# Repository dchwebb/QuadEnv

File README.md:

# QuadEnv/L4O

Overview
--------

QuadEnv is a four-voice polyphonic ADSR envelope generator designed for use with the Eurorack Modular Synthesiser architecture. L4O is a four-voice sine wave LFO and uses the same hardware as QuadEnv.

Different front panels are provided for each mode, while the firmware, component and controls boards are dual mode.

As part of a range of compatilble Mountjoy Modular modules, polyphonic interconnections are made using RJ-45 cables (as used for Ethernet).

A USB serial console is provided for customising the envelope times and fade-in rates of the LFOs.

The third potentiometer (Sustain or Fade-In) has a momentary button which allows switching between the envelope and LFO modes via a long press.

QuadEnv
-------

The digital envelopes are modelled on a Roland System 100 system, with logarithmic/exponential attack/decay and release sections. The level of each envelope is displayed in a bank of LEDs at the top of the module.

A short press on the Sustain potentiometer button inverts the envelopes.

The USB serial console allows the envelope times to be scaled up or down for longer or shorter envelopes.

L4O
---

The four potentiometers control Speed, Spread, Fade-in and Level. Spread adjusts the variation in LFO speed from one voice to another. Fade-in allows the LFO level to be increased gradually. Short pressing the Fade-in button allows the speed to also be gradually increased. Fade-in starts when a gate is received at the input.

The USB serial interface allows the fade-in times of the level and speed to be independently adjusted.

Technical
---------

The module is based around an STM32G431 microcontroller which contains four internal 12 bit DACs used to generate the envelopes at approximately 47kHz.

A CD40109B level shifter provides input protection for the Gate In signals. A TL074 op-amp ampilifies the DAC outputs to around 8 volts at maximum.

Construction is a sandwich of three PCBs with a component board, a controls board and a panel. PCBs designed in Kicad v6.

From version 3 LEDs are controlled by PWM to fix no display when under the LED forward voltage.

[Components schematic v3](https://raw.githubusercontent.com/dchwebb/QuadEnv/master/Component_Schematic_v3.pdf)

[Controls schematic v2](https://raw.githubusercontent.com/dchwebb/QuadEnv/master/Control_Schematic.pdf)

### Power

The Eurorack +/-12V rails have reverse polarity protection and filtering. 3.3V rails are generated with a linear regulator.

- +12V Maximum Current Draw: 80mA

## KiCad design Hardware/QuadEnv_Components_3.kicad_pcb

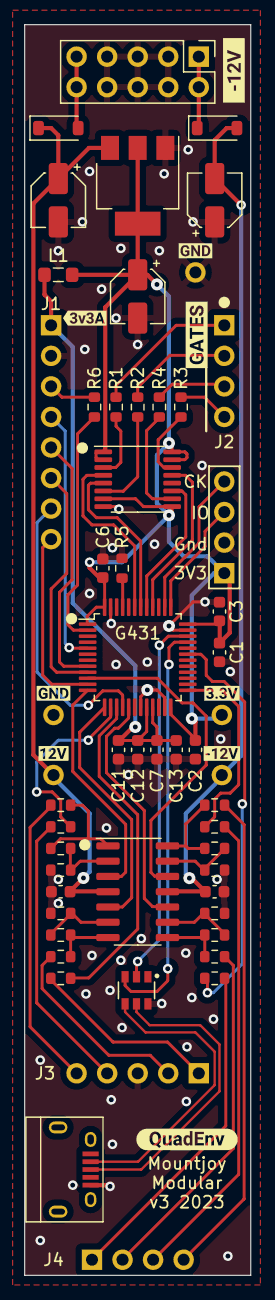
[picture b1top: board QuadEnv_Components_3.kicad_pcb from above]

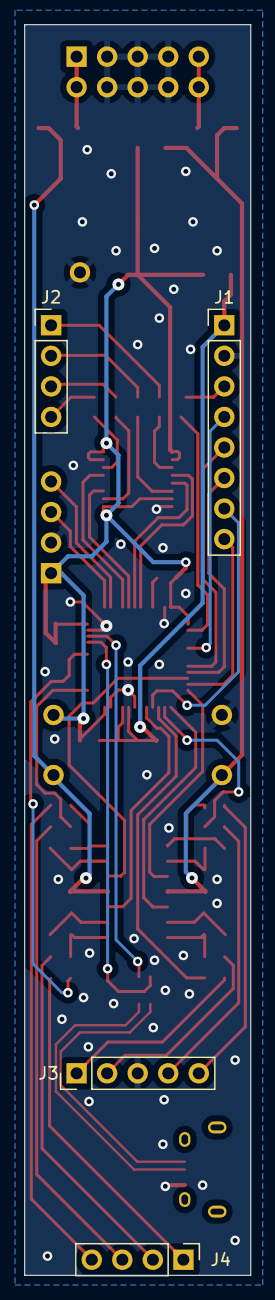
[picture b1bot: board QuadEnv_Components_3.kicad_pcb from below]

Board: 2 copper layers, 18.8 x 104.0 mm, 64 parts (4 on the bottom side), 57 nets.

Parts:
C1: 4.7uF; C_0603_1608Metric
C2, C3, C6, C12: 100nF; C_0603_1608Metric
C4, C5, C8: 22uF; CP_Elec_4x5.8
C7: 10nF; C_0603_1608Metric
C9, C10, C11, C13: 1uF; C_0603_1608Metric
D1, D2: 1N5819; D_SOD-123
J1: Conn_01x08_Male; PinHeader_1x08_P2.54mm_Vertical
J2, J4: Conn_01x04_Male; PinHeader_1x04_P2.54mm_Vertical
J3: Conn_01x05_Male; PinHeader_1x05_P2.54mm_Vertical
J5: SWD_Header; SWD_header
J6: Eurorack_10_pin_power; PinHeader_2x05_P2.54mm_Vertical
J7: USB_B_Micro; USB_Micro-B_Amphenol
L1: L_Small; L_0805_2012Metric_Pad1.05x1.20mm_HandSolder
R1, R2, R3, R4: 10k; R_0603_1608Metric
R5: 100k; R_0603_1608Metric
R6: 510; R_0603_1608Metric
R9, R10, R11, R12: 3k3; R_0603_1608Metric
R13, R14, R15, R16: 4k7; R_0603_1608Metric
R17, R18, R19, R20, R21, R22, R23, R24: 1k; R_0603_1608Metric
TP1, TP2, TP3, TP4, TP5: TestPoint; 1mm_Test_Point
U1: STM32G431C6T6; LQFP-48_7x7mm_P0.5mm
U2: LD1117-3.3-4Tab; SOT-223-3_TabPin2
U3: CD40109B; TSSOP-16_4.4x5mm_P0.65mm
U4: TL074; SOIC-14_3.9x8.7mm_P1.27mm
U5: STF202-22T1G
kibuzzard-64DF8AE0: G***; kibuzzard-64DF8AE0
kibuzzard-640A0C12: G***; kibuzzard-640A0C12
kibuzzard-6409F893: G***; kibuzzard-6409F893
kibuzzard-6409FE2B: G***; kibuzzard-6409FE2B
kibuzzard-6409FE16: G***; kibuzzard-6409FE16
kibuzzard-6409FE46: G***; kibuzzard-6409FE46
kibuzzard-6409FE57, kibuzzard-6409FE57#2: G***; kibuzzard-6409FE57
kibuzzard-6409FEF9: G***; kibuzzard-6409FEF9

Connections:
+3.3V: C1.1, C2.1, C3.1, C6.1, C8.1, J5.1, L1.1, TP2.1, U1.1 (VBAT), U1.24 (VDD), U1.36 (VDD), U1.48 (VDD), U2.2 (VO), U3.1 (Vcc), U3.2 (EN_A), U3.7 (EN_B), U3.9 (EN_C), U3.15 (EN_D), U3.16 (Vdd)
+3.3VA: C7.1, C11.2, C12.2, C13.2, J1.1, L1.2, U1.20 (VREF+), U1.21 (VDDA)
+12V: C4.1, C9.2, D1.1 (K), TP3.1, U2.3 (VI), U4.4 (V+)
-12V: C5.2, C10.2, D2.2 (A), TP4.1, U4.11 (V-)
/+12V_IN: D1.2 (A), J6.9, J6.10
/-12V_IN: D2.1 (K), J6.1, J6.2
/Attack_Pot: J1.5, U1.8 (PA0)
/BOOT0: R5.2, U1.45 (PB8-BOOT0)
/D+: J7.3 (D+), U5.5 (D1_IN)
/D-: J7.2 (D-), U5.4 (D2_IN)
/Decay_Pot: J1.6, U1.9 (PA1)
/Env1_DAC: U1.12 (PA4), U4.3 (+)
/Env1_Out: J3.5, R18.2
/Env2_DAC: U1.13 (PA5), U4.5 (+)
/Env2_Out: J3.2, R20.2
/Env3_DAC: U1.17 (PB1), U4.10 (+)
/Env3_Out: J4.2, R22.2
/Env4_DAC: U1.10 (PA2), U4.12 (+)
/Env4_Out: J4.4, R24.2
/Gate1: U1.43 (PB6), U3.4 (E)
/Gate1_In: J2.1, R1.1
/Gate2: U1.42 (PB5), U3.5 (F)
/Gate2_In: J2.2, R2.1
/Gate3: U1.41 (PB4), U3.11 (G)
/Gate3_In: J2.3, R4.2
/Gate4: U1.40 (PB3), U3.13 (H)
/Gate4_In: J2.4, R3.2
/LED1: R17.1, U1.14 (PA6)
/LED2: R19.1, U1.15 (PA7)
/LED3: R21.1, U1.31 (PA9)
/LED4: R23.1, U1.25 (PB11)
/Led1_Out: J3.4, R17.2
/Led2_Out: J3.1, R19.2
/Led3_Out: J4.1, R21.2
/Led4_Out: J4.3, R23.2
/Mode_Btn: J1.4, U1.5 (PF0-OSC_IN)
/Mode_Led: J1.3, R6.1
/Release_Pot: J1.8, U1.11 (PA3)
/SWCLK: J5.4, U1.38 (PA14)
/SWIO: J5.3, U1.37 (PA13)
/Sustain_Pot: J1.7, U1.16 (PB0)
/USB_DM: U1.33 (PA11), U5.3 (D2_OUT)
/USB_DP: U1.34 (PA12), U5.2 (D1_OUT)
GND: C1.2, C2.2, C3.2, C4.2, C5.1, C6.2, C7.2, C8.2, C9.1, C10.1, C11.1, C12.1, C13.1, J1.2, J3.3, J5.2, J6.3, J6.4, J6.5, J6.6, J6.7, J6.8, J7.5 (GND), R5.1, R9.2, R10.2, R11.2, R12.2, TP1.1, TP5.1, U1.19 (VSSA), U1.23 (VSS), U1.35 (VSS), U1.47 (VSS), U2.1 (GND), U3.8 (Vss), U5.6 (GND)
unnamed: R13.1, R18.1, U4.1
unnamed: R14.1, R20.1, U4.7
unnamed: R15.1, R22.1, U4.8
unnamed: R16.1, R24.1, U4.14
unnamed: R6.2, U1.2 (PC13)
unnamed: R1.2, U3.3 (A)
unnamed: R2.2, U3.6 (B)
unnamed: R4.1, U3.10 (C)
unnamed: R3.1, U3.14 (D)
unnamed: R9.1, R13.2, U4.2 (-)
unnamed: R10.1, R14.2, U4.6 (-)
unnamed: R11.1, R15.2, U4.9 (-)
unnamed: R12.1, R16.2, U4.13 (-)

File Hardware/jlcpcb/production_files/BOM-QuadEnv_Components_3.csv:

Comment,Designator,Footprint,LCSC
100nF,"C12,C2,C3,C6",C_0603_1608Metric,C14663
1uF,"C10,C11,C13,C9",C_0603_1608Metric,C15849
4.7uF,C1,C_0603_1608Metric,C19666
1k,"R17,R18,R19,R20,R21,R22,R23,R24",R_0603_1608Metric,C21190
3k3,"R10,R11,R12,R6,R9",R_0603_1608Metric,C22978
10k,"R1,R13,R14,R15,R16,R2,R3,R4",R_0603_1608Metric,C23162
100k,R5,R_0603_1608Metric,C25803
10nF,C7,C_0603_1608Metric,C57112
LD1117-3.3-4Tab,U2,SOT-223-3_TabPin2,C6186
1N5819,"D1,D2",D_SOD-123,C8598

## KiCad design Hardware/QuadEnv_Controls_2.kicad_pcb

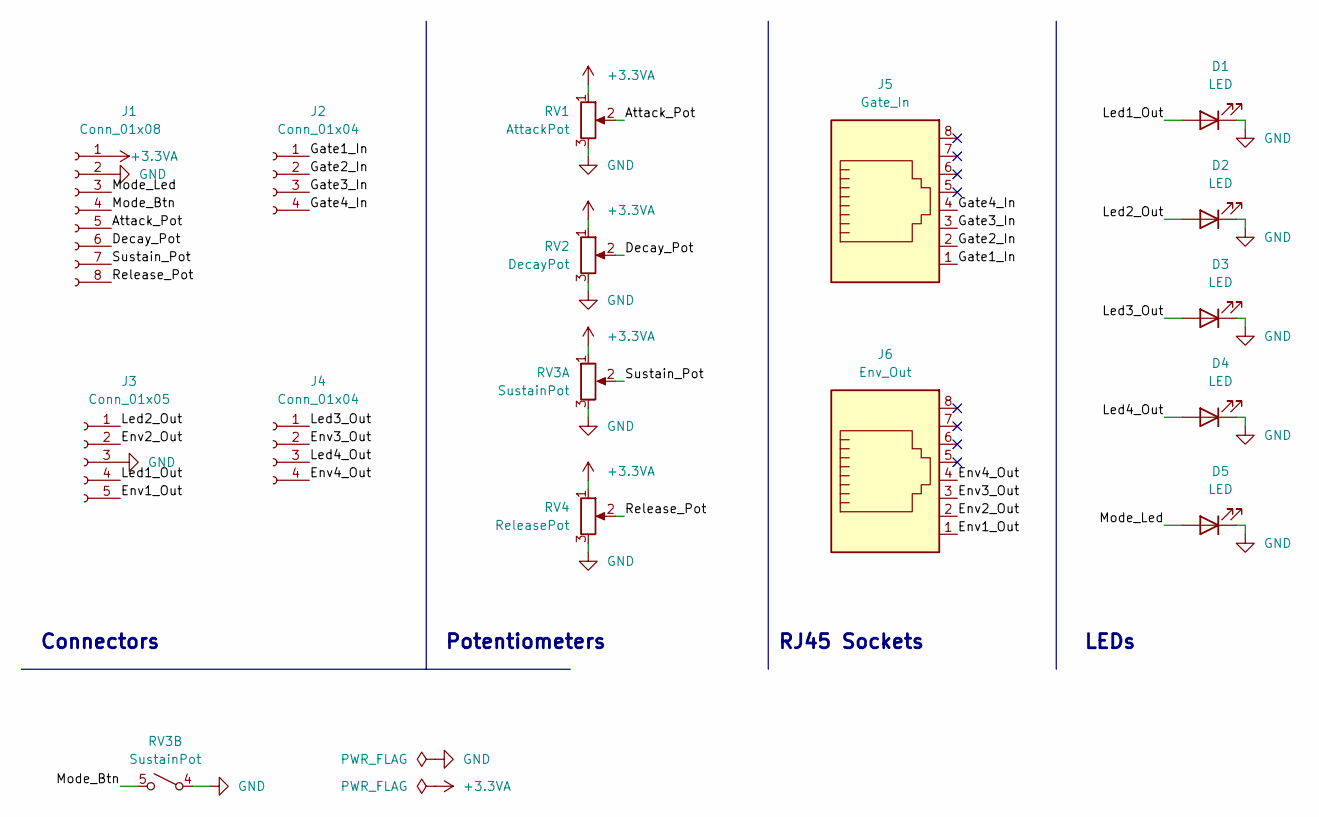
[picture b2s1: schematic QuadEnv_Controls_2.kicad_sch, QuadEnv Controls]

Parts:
D1, D2, D3, D4, D5: LED; LED_D3.0mm
J1: Conn_01x08; PinSocket_1x08_P2.54mm_Vertical
J2, J4: Conn_01x04; PinSocket_1x04_P2.54mm_Vertical
J3: Conn_01x05; PinSocket_1x05_P2.54mm_Vertical
J5: Gate_In; RJ45_Amphenol_RJHSE-3080
J6: Env_Out; RJ45_Amphenol_RJHSE-3080
RV1: AttackPot; Alpha_9mm_Potentiometer_Aligned
RV2: DecayPot; Alpha_9mm_Potentiometer_Aligned
RV3: SustainPot; Bourns_Switch_Potentiometer
RV4: ReleasePot; Alpha_9mm_Potentiometer_Aligned

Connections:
+3.3VA: J1.1, RV1.1, RV2.1, RV3.1, RV4.1
/Attack_Pot: J1.5, RV1.2
/Decay_Pot: J1.6, RV2.2
/Env1_Out: J3.5, J6.1
/Env2_Out: J3.2, J6.2
/Env3_Out: J4.2, J6.3
/Env4_Out: J4.4, J6.4
/Gate1_In: J2.1, J5.1
/Gate2_In: J2.2, J5.2
/Gate3_In: J2.3, J5.3
/Gate4_In: J2.4, J5.4
/Led1_Out: D1.2 (A), J3.4
/Led2_Out: D2.2 (A), J3.1
/Led3_Out: D3.2 (A), J4.1
/Led4_Out: D4.2 (A), J4.3
/Mode_Btn: J1.4, RV3.5 (2)
/Mode_Led: D5.2 (A), J1.3
/Release_Pot: J1.8, RV4.2
/Sustain_Pot: J1.7, RV3.2
GND: D1.1 (K), D2.1 (K), D3.1 (K), D4.1 (K), D5.1 (K), J1.2, J3.3, RV1.3, RV2.3, RV3.3, RV3.4 (1), RV4.3

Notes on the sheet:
Potentiometers
Connectors
LEDs
RJ45 Sockets

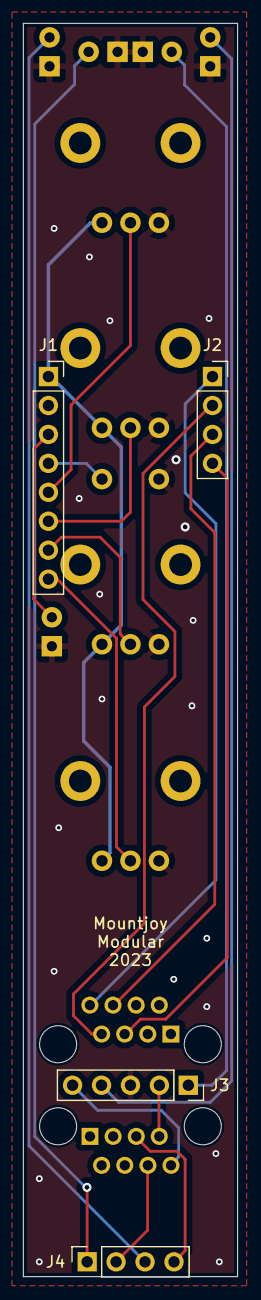
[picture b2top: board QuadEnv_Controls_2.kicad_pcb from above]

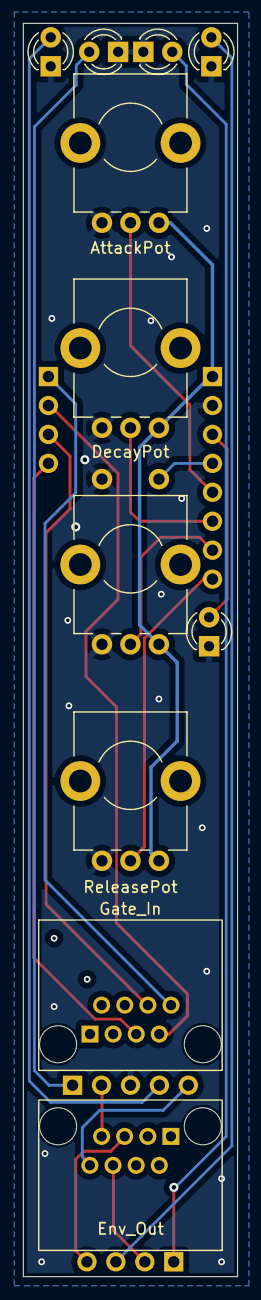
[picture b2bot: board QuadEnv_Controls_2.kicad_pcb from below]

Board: 2 copper layers, 18.8 x 110.0 mm, 15 parts (11 on the bottom side), 20 nets.

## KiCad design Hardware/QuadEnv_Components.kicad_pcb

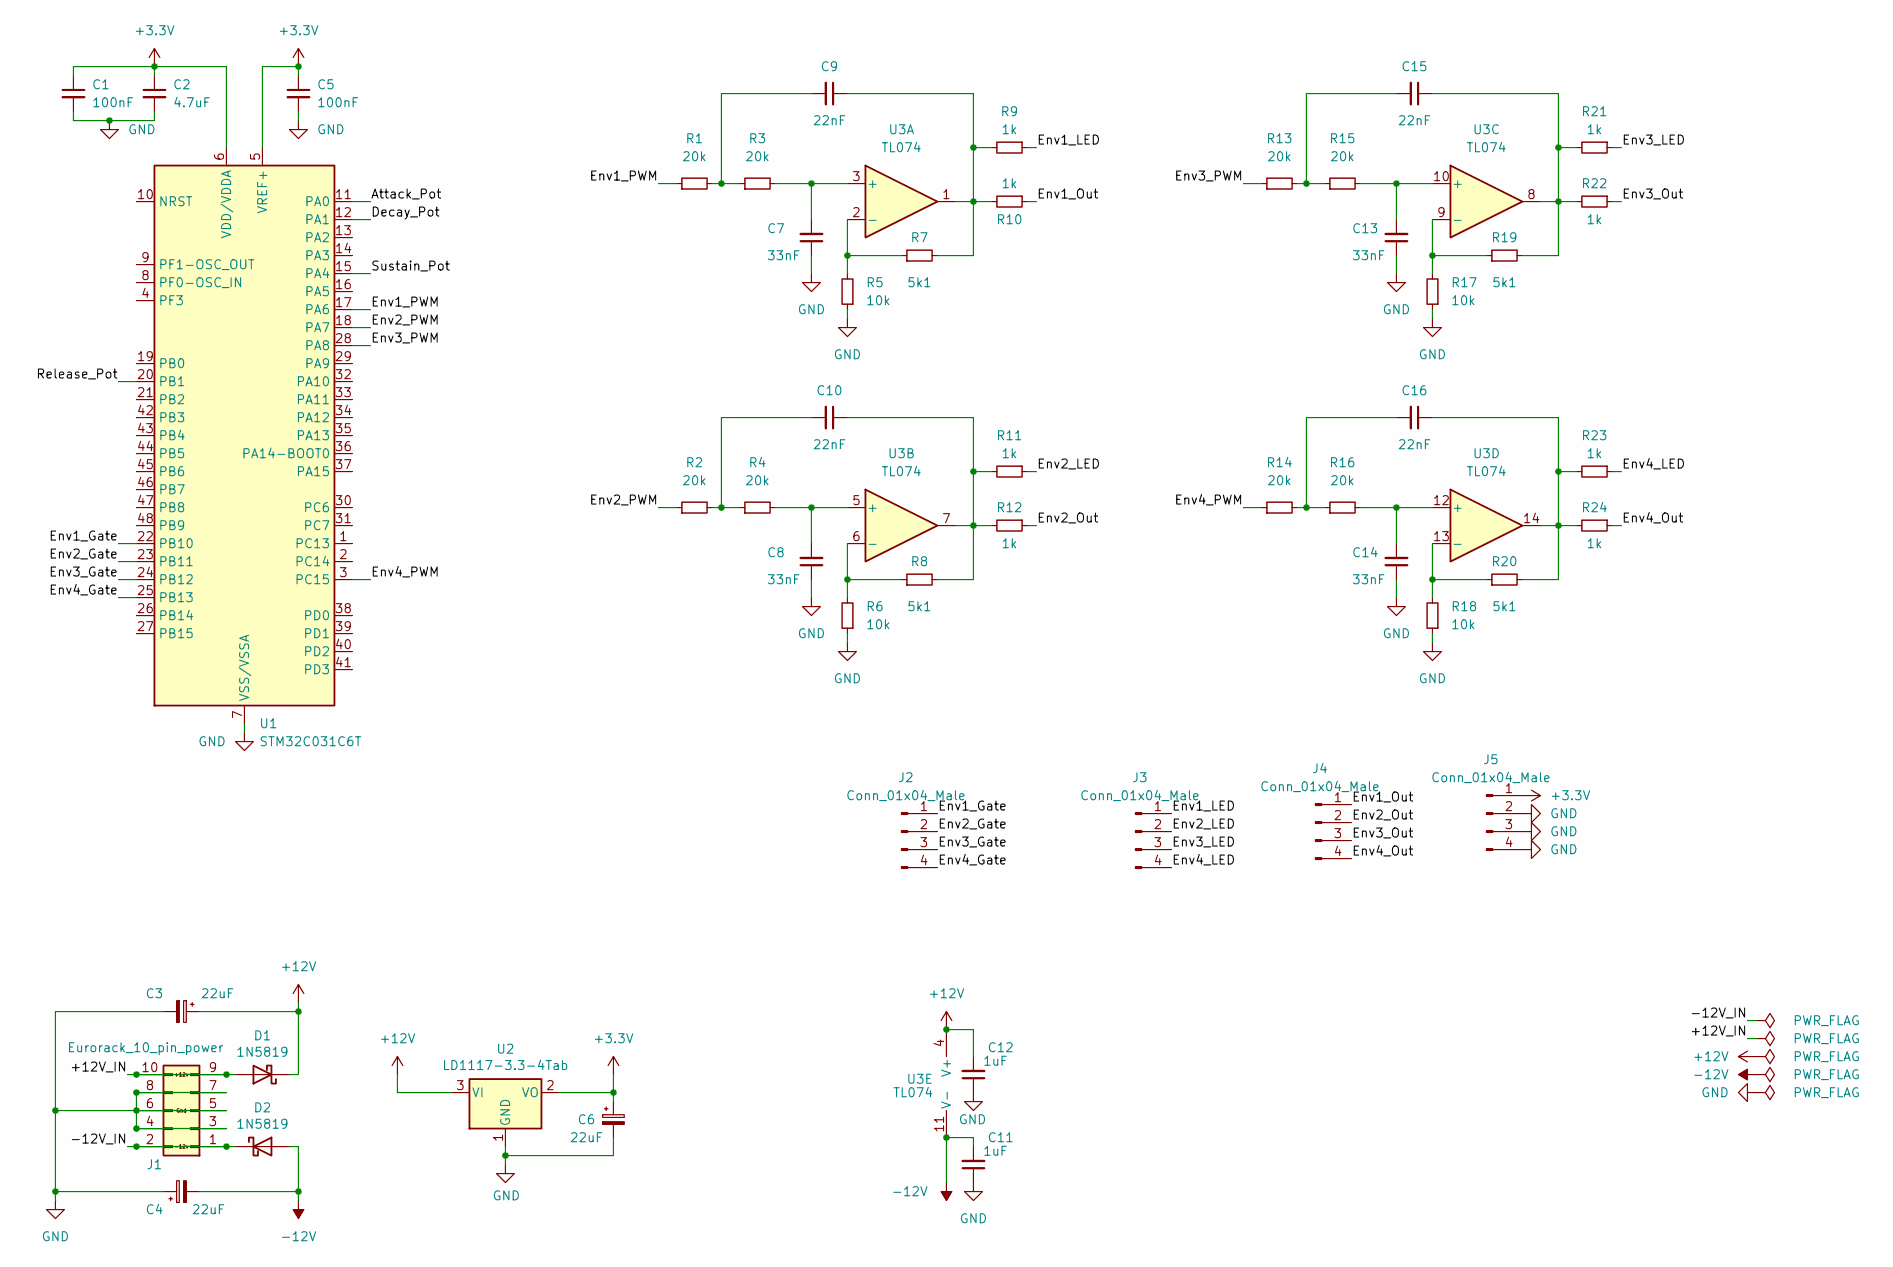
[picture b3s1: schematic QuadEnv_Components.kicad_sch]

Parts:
C1, C5: 100nF; C_0603_1608Metric
C2: 4.7uF; C_0603_1608Metric
C3: 22uF; CP_Elec_4x5.8; Part_Number C134798
C4, C6: 22uF; CP_Elec_4x5.8; Part_Number C134793
C7, C8, C13, C14: 33nF; C_0603_1608Metric
C9, C10, C15, C16: 22nF; C_0603_1608Metric
C11, C12: 1uF; C_0603_1608Metric
D1, D2: 1N5819; D_SOD-123; Part_Number C8598
J1: Eurorack_10_pin_power; Eurorack_10_pin_header
J2, J3, J4, J5: Conn_01x04_Male; PinHeader_1x04_P2.54mm_Vertical
R1, R2, R3, R4, R13, R14, R15, R16: 20k; R_0603_1608Metric
R5, R6, R17, R18: 10k; R_0603_1608Metric
R7, R8, R19, R20: 5k1; R_0603_1608Metric
R9, R10, R11, R12, R21, R22, R23, R24: 1k; R_0603_1608Metric
U1: STM32C031C6T; LQFP-48_7x7mm_P0.5mm
U2: LD1117-3.3-4Tab; SOT-223-3_TabPin2
U3: TL074; SOIC-14_3.9x8.7mm_P1.27mm

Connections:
+3.3V: C1.1, C2.1, C5.1, C6.1, J5.1, U1.5 (VREF+), U1.6 (VDD/VDDA), U2.2 (VO)
+12V: C3.1, C12.2, D1.1 (K), U2.3 (VI), U3.4 (V+)
-12V: C4.2, C11.2, D2.2 (A), U3.11 (V-)
/+12V_IN: D1.2 (A), J1.9, J1.10
/-12V_IN: D2.1 (K), J1.1, J1.2
/Attack_Pot: U1.11 (PA0)
/Decay_Pot: U1.12 (PA1)
/Env1_Gate: J2.1, U1.22 (PB10)
/Env1_LED: J3.1, R9.1
/Env1_Out: J4.1, R10.1
/Env1_PWM: R1.1, U1.17 (PA6)
/Env2_Gate: J2.2, U1.23 (PB11)
/Env2_LED: J3.2, R11.1
/Env2_Out: J4.2, R12.1
/Env2_PWM: R2.1, U1.18 (PA7)
/Env3_Gate: J2.3, U1.24 (PB12)
/Env3_LED: J3.3, R21.1
/Env3_Out: J4.3, R22.1
/Env3_PWM: R13.1, U1.28 (PA8)
/Env4_Gate: J2.4, U1.25 (PB13)
/Env4_LED: J3.4, R23.1
/Env4_Out: J4.4, R24.1
/Env4_PWM: R14.1, U1.3 (PC15), U1.46 (PB7)
/Release_Pot: U1.20 (PB1)
/Sustain_Pot: U1.15 (PA4)
GND: C1.2, C2.2, C3.2, C4.1, C5.2, C6.2, C7.1, C8.1, C11.1, C12.1, C13.1, C14.1, J1.3, J1.4, J1.5, J1.6, J1.7, J1.8, J5.2, J5.3, J5.4, R5.1, R6.1, R17.1, R18.1, U1.7 (VSS/VSSA), U2.1 (GND)
unnamed: C7.2, R3.2, U3.3 (+)
unnamed: C8.2, R4.2, U3.5 (+)
unnamed: C9.1, R7.2, R9.2, R10.2, U3.1
unnamed: C9.2, R1.2, R3.1
unnamed: C10.1, R8.2, R11.2, R12.2, U3.7
unnamed: C10.2, R2.2, R4.1
unnamed: C13.2, R15.2, U3.10 (+)
unnamed: C14.2, R16.2, U3.12 (+)
unnamed: C15.1, R19.2, R21.2, R22.2, U3.8
unnamed: C15.2, R13.2, R15.1
unnamed: C16.1, R20.2, R23.2, R24.2, U3.14
unnamed: C16.2, R14.2, R16.1
unnamed: R5.2, R7.1, U3.2 (-)
unnamed: R6.2, R8.1, U3.6 (-)
unnamed: R17.2, R19.1, U3.9 (-)
unnamed: R18.2, R20.1, U3.13 (-)

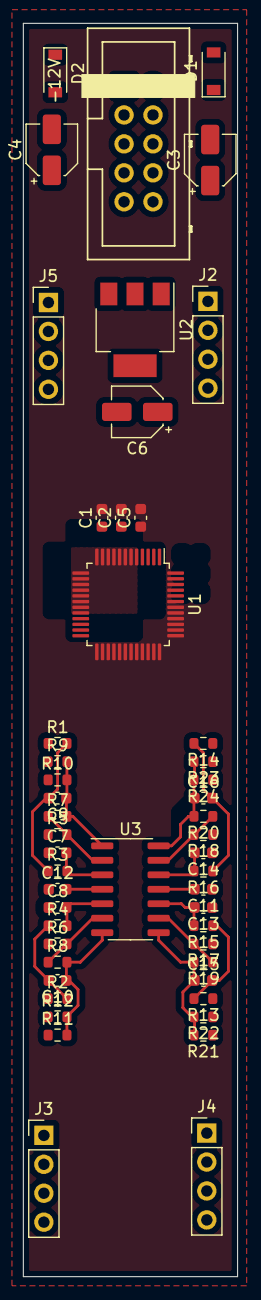
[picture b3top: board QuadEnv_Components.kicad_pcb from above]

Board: 2 copper layers, 18.8 x 110.0 mm, 50 parts (0 on the bottom side), 38 nets.

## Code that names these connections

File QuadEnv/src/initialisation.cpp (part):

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
void InitDAC()
{
	// Configure 4 DAC outputs PA4 and PA5 are regular DAC1 buffered outputs; PA2 and PB1 are DAC3 via OpAmp1 and OpAmp3 (Manual p.789)

	RCC->AHB2ENR |= RCC_AHB2ENR_GPIOAEN;			// Enable GPIO Clock
	RCC->AHB2ENR |= RCC_AHB2ENR_GPIOBEN;			// Enable GPIO Clock
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	RCC->AHB2ENR |= RCC_AHB2ENR_DAC3EN;				// Enable DAC Clock

	DAC1->MCR &= ~DAC_MCR_MODE1_Msk;				// Set to normal mode: DAC channel1 is connected to external pin with Buffer enabled
	DAC1->CR |= DAC_CR_EN1;							// Enable DAC using PA4 (DAC_OUT1)

	DAC1->MCR &= ~DAC_MCR_MODE2_Msk;				// Set to normal mode: DAC channel2 is connected to external pin with Buffer enabled
	DAC1->CR |= DAC_CR_EN2;							// Enable DAC using PA5 (DAC_OUT2)

	// output triggered with DAC->DHR12R1 = x;

	// Opamp for DAC3 Channel 1: Follower configuration mode - output on PA2
	DAC3->MCR |= DAC_MCR_MODE1_0 | DAC_MCR_MODE1_1;	// 011: DAC channel1 is connected to on chip peripherals with Buffer disabled
	DAC3->CR |= DAC_CR_EN1;							// Enable DAC

	OPAMP1->CSR |= OPAMP_CSR_VMSEL;					// 11: Opamp_out connected to OPAMPx_VINM input
	OPAMP1->CSR |= OPAMP_CSR_VPSEL;					// 11: DAC3_CH1  connected to OPAMP1 VINP input
	OPAMP1->CSR |= OPAMP_CSR_OPAMPxEN;				// Enable OpAmp: voltage on pin OPAMPx_VINP is buffered to pin OPAMPx_VOUT (PA2)

	// Opamp for DAC3 Channel 2: Follower configuration mode - output on PB1
	// NB According to manual p.790 this should only work on category 3/4 devices and STM32G431 is category 2, but tested working
	DAC3->MCR |= DAC_MCR_MODE2_0 | DAC_MCR_MODE2_1;	// 011: DAC channel2 is connected to on chip peripherals with Buffer disabled
	DAC3->CR |= DAC_CR_EN2;							// Enable DAC

	OPAMP3->CSR |= OPAMP_CSR_VMSEL;					// 11: Opamp_out connected to OPAMPx_VINM input
	OPAMP3->CSR |= OPAMP_CSR_VPSEL;					// 11: DAC3_CH2  connected to OPAMP1 VINP input
	OPAMP3->CSR |= OPAMP_CSR_OPAMPxEN;				// Enable OpAmp: voltage on pin OPAMPx_VINP is buffered to pin OPAMPx_VOUT (PB1)
}


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	RCC->AHB2ENR |= RCC_AHB2ENR_GPIOCEN;			// Reset and clock control - GPIO port C
	RCC->AHB2ENR |= RCC_AHB2ENR_GPIOFEN;			// Reset and clock control - GPIO port F

	// NB PB6 is used in USB Power delivery and by default has a pull down to ground - disable in the PWR register (datasheet p.60 note 5)
	PWR->CR3 |= PWR_CR3_UCPD_DBDIS;

	GPIOB->MODER &= ~GPIO_MODER_MODER6;				// configure PB6 gate 1 input
	GPIOB->MODER &= ~GPIO_MODER_MODER5;				// configure PB5 gate 2 input
	GPIOB->MODER &= ~GPIO_MODER_MODER4;				// configure PB4 gate 3 input
	GPIOB->MODER &= ~GPIO_MODER_MODER3;				// configure PB3 gate 4 input

	GPIOF->MODER &= ~GPIO_MODER_MODER0;				// PF0 Fade-in Button input
	GPIOF->PUPDR |= GPIO_PUPDR_PUPD0_0;				// 00: None; *01: Pull-up; 10: Pull-down

	GPIOC->MODER &= ~GPIO_MODER_MODE13_1;			// PC13 LED Out
}


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
	/*--------------------------------------------------------------------------------------------
	Configure ADC Channels to be converted:
	0	PA0 ADC12_IN1		Env Attack
	1	PA1 ADC12_IN2		Env Decay
	2	PB0 ADC1_IN15		Env Sustain
	3	PA3 ADC1_IN4		Env Release
	*/

	InitAdcPins(ADC1, {1, 2, 15, 4});
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void InitPWMTimer()
{
	// LED PWM:
	// Led1  PA6   TIM3_CH1  AF2
	// Led2  PA7   TIM3_CH2  AF2
	// Led3  PA9   TIM2_CH3  AF10
	// Led4  PB11  TIM2_CH4  AF1
	RCC->AHB2ENR |= RCC_AHB2ENR_GPIOAEN;			// reset and clock control - advanced high performance bus - GPIO port A
	RCC->AHB2ENR |= RCC_AHB2ENR_GPIOBEN;			// reset and clock control - advanced high performance bus - GPIO port B
	RCC->APB1ENR1 |= RCC_APB1ENR1_TIM2EN;
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
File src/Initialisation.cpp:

#include "Initialisation.h"


void SystemClock_Config()
{

	volatile uint32_t tmpreg [[maybe_unused]];

	// Enable the APB2 peripheral clock
	SET_BIT(RCC->APBENR2, RCC_APBENR2_SYSCFGEN);
	tmpreg = READ_BIT(RCC->APBENR2, RCC_APBENR2_SYSCFGEN);	// Delay after an RCC peripheral clock enabling

	SET_BIT(RCC->APBENR1, RCC_APBENR1_PWREN);				// Power interface clock enable
	tmpreg = READ_BIT(RCC->APBENR1, RCC_APBENR1_PWREN);		// Delay after an RCC peripheral clock enabling

	// Calibration to adjust frequency of the internal HSI RC
#define RCC_HSICALIBRATION_DEFAULT     64U					// Default HSI calibration trimming value

	MODIFY_REG(RCC->ICSCR, RCC_ICSCR_HSITRIM, RCC_HSICALIBRATION_DEFAULT << RCC_ICSCR_HSITRIM_Pos);

	MODIFY_REG(RCC->CR, RCC_CR_HSIDIV, 0);					// HSI48 clock division factor 0 = 1; default = 4

	MODIFY_REG(FLASH->ACR, FLASH_ACR_LATENCY, 1);			// Set Flash Latency to 1 wait state
	while ((FLASH->ACR & FLASH_ACR_LATENCY) != 1);			// Wait until Flash Latency has been set

	// Leave other clock dividers at default (fastest)
}

void InitSysTick()
{
	SysTick_Config(SystemCoreClock / SYSTICK);		// gives 1ms
	NVIC_SetPriority(SysTick_IRQn, 0);
}


void InitIO()
{
	// MODER 00: Input mode, 01: General purpose output mode, 10: Alternate function mode, 11: Analog mode (reset state)

	RCC->IOPENR |= RCC_IOPENR_GPIOAEN;			// reset and clock control - advanced high performance bus - GPIO port A
	RCC->IOPENR |= RCC_IOPENR_GPIOBEN;			// reset and clock control - advanced high performance bus - GPIO port B
	RCC->IOPENR |= RCC_IOPENR_GPIOCEN;			// reset and clock control - advanced high performance bus - GPIO port C

	GPIOC->MODER &= ~GPIO_MODER_MODE13;			// configure PC13 gate 1 input

	GPIOA->MODER &= ~GPIO_MODER_MODE5_1;		// Configure PA5 as LED output

//	GPIOB->MODER &= ~GPIO_MODER_MODER5;			// configure PB5  Env 1 Short input

//	GPIOB->PUPDR |= GPIO_PUPDR_PUPDR5_0;		// configure PB5  Env 1 Pull-up
}


void InitPWMTimer()
{
	// TIM3: Channel 1: *PA6 (AF1), PB4 (AF1), PB8 (AF3), PB6 (AF12), PB7 (AF11), PC6 (AF1)
	// 		 Channel 2: *PA7 (AF1), PB3 (AF3), PB5 (AF1), PB9 (AF3), PB6 (AF13), PC7 (AF1), PC14 (AF11)
	// 		 Channel 3: *PA8 (AF11), PB0 (AF1), PB5 (AF3), PB6 (AF3), PC15 (AF3)
	// 		 Channel 4: PA8 (AF12), PB1 (AF1), PB7 (AF3), PB6 (AF3), *PC15 (AF3)
	RCC->IOPENR |= RCC_IOPENR_GPIOAEN;
	RCC->IOPENR |= RCC_IOPENR_GPIOBEN;
	RCC->APBENR1 |= RCC_APBENR1_TIM3EN;

	// Enable channel 1, 2, 3 PWM output pins on PA6, PA7, PA8
	GPIOA->MODER &= ~(GPIO_MODER_MODE6_0 | GPIO_MODER_MODE7_0 | GPIO_MODER_MODE8_0);	// 00: Input mode; 01: General purpose output mode; 10: Alternate function mode; 11: Analog mode (default)
	GPIOA->AFR[0] |= (GPIO_AFRL_AFSEL6_0 | GPIO_AFRL_AFSEL7_0);		// AF1
	GPIOA->AFR[1] |= 11 << GPIO_AFRH_AFSEL8_Pos;					// AF11

	// Enable channel 4 PWM output pin on PC15
	GPIOC->MODER &= ~GPIO_MODER_MODE15_0;
	GPIOC->AFR[1] |= 3 << GPIO_AFRH_AFSEL15_Pos;					// AF3

	// Timing calculations: Clock = 64MHz / (PSC + 1) = 32m counts per second
	// ARR = number of counts per PWM tick = 4096
	// 32m / ARR = 7.812kHz of PWM square wave with 4096 levels of output
	TIM3->CCMR1 |= TIM_CCMR1_OC1PE;					// Output compare 1 preload enable
	TIM3->CCMR1 |= TIM_CCMR1_OC2PE;					// Output compare 2 preload enable
	TIM3->CCMR2 |= TIM_CCMR2_OC3PE;					// Output compare 3 preload enable
	TIM3->CCMR2 |= TIM_CCMR2_OC4PE;					// Output compare 4 preload enable

	TIM3->CCMR1 |= (TIM_CCMR1_OC1M_1 | TIM_CCMR1_OC1M_2);	// 0110: PWM mode 1 - In upcounting, channel 1 active if TIMx_CNT<TIMx_CCR1
	TIM3->CCMR1 |= (TIM_CCMR1_OC2M_1 | TIM_CCMR1_OC2M_2);	// 0110: PWM mode 1 - In upcounting, channel 2 active if TIMx_CNT<TIMx_CCR2
	TIM3->CCMR2 |= (TIM_CCMR2_OC3M_1 | TIM_CCMR2_OC3M_2);	// 0110: PWM mode 1 - In upcounting, channel 3 active if TIMx_CNT<TIMx_CCR3
	TIM3->CCMR2 |= (TIM_CCMR2_OC4M_1 | TIM_CCMR2_OC4M_2);	// 0110: PWM mode 1 - In upcounting, channel 3 active if TIMx_CNT<TIMx_CCR3

	TIM3->CCR1 = 0;									// Initialise PWM level to 0
	TIM3->CCR2 = 0;
	TIM3->CCR3 = 0;
	TIM3->CCR4 = 0;

	TIM3->ARR = pwmLength - 1;						// Total number of PWM ticks = 512
	TIM3->PSC = 0;									// Should give ~93.7kHz
	TIM3->CR1 |= TIM_CR1_ARPE;						// 1: TIMx_ARR register is buffered
	TIM3->CCER |= (TIM_CCER_CC1E | TIM_CCER_CC2E | TIM_CCER_CC3E | TIM_CCER_CC4E);		// Capture mode enabled / OC1 signal is output on the corresponding output pin
	TIM3->EGR |= TIM_EGR_UG;						// 1: Re-initialize the counter and generates an update of the registers

	// Generate interrupt on Update
	TIM3->DIER |= TIM_DIER_UIE;						// DMA/interrupt enable register
	NVIC_EnableIRQ(TIM3_IRQn);
	NVIC_SetPriority(TIM3_IRQn, 0);					// Lower is higher priority

	TIM3->CR1 |= TIM_CR1_CEN;						// Enable counter
}


void InitADC(volatile uint16_t* ADC_array)
{
	// Initialize Clocks
	RCC->AHBENR |= RCC_AHBENR_DMA1EN;
	RCC->APBENR2 |= RCC_APBENR2_ADCEN;
	//RCC->CCIPR |= RCC_CCIPR_ADCSEL_1;				// 00: System clock (Default); 0b10: HSIKER

	DMA1_Channel1->CCR &= ~DMA_CCR_EN;
	DMA1_Channel1->CCR |= DMA_CCR_CIRC;				// Circular mode to keep refilling buffer
	DMA1_Channel1->CCR |= DMA_CCR_MINC;				// Memory in increment mode
	DMA1_Channel1->CCR |= DMA_CCR_PSIZE_0;			// Peripheral size: 8 bit; 01 = 16 bit; 10 = 32 bit
	DMA1_Channel1->CCR |= DMA_CCR_MSIZE_0;			// Memory size: 8 bit; 01 = 16 bit; 10 = 32 bit
	DMA1_Channel1->CCR |= DMA_CCR_PL_0;				// Priority: 00 = low; 01 = Medium; 10 = High; 11 = Very High

	DMA1->IFCR = 0x3F << DMA_IFCR_CGIF1_Pos;		// clear all five interrupts for this stream

	DMAMUX1_Channel0->CCR |= 5; 					// DMA request MUX input 5 = ADC (See p.201)
	DMAMUX1_ChannelStatus->CFR |= DMAMUX_CFR_CSOF0; // Channel 1 Clear synchronization overrun event flag

	ADC1->CR |= ADC_CR_ADVREGEN;					// Enable ADC internal voltage regulator

	// Wait until voltage regulator settled
	volatile uint32_t wait_loop_index = (SystemCoreClock / (100000UL * 2UL));
	while (wait_loop_index != 0UL) {
		wait_loop_index--;
	}
	while ((ADC1->CR & ADC_CR_ADVREGEN) != ADC_CR_ADVREGEN) {}

	//ADC12_COMMON->CCR |= ADC_CCR_CKMODE;			// adc_hclk/4 (Synchronous clock mode)
	ADC1->CFGR1 |= ADC_CFGR1_CONT;					// 1: Continuous conversion mode for regular conversions
	ADC1->CFGR1 |= ADC_CFGR1_OVRMOD;				// Overrun Mode 1: ADC_DR register is overwritten with the last conversion result when an overrun is detected.
	ADC1->CFGR1 |= ADC_CFGR1_DMACFG;				// 0: DMA One Shot Mode selected, 1: DMA Circular Mode selected
	ADC1->CFGR1 |= ADC_CFGR1_DMAEN;					// Enable ADC DMA

	// A0 = PA0 (ADC_IN0); A1 = PA1 (ADC_IN1); A2 = PA4 (ADC_IN4); A3 = PB1 (ADC_IN18)
	ADC1->CFGR1 &= ~ADC_CFGR1_CHSELRMOD;			// In this mode bits in ADC_CHSELR activate inputs
	ADC1->CHSELR |= ADC_CHSELR_CHSEL0 | ADC_CHSELR_CHSEL1 | ADC_CHSELR_CHSEL4 | ADC_CHSELR_CHSEL18;

	// Start calibration
	ADC1->CR |= ADC_CR_ADCAL;
	while ((ADC1->CR & ADC_CR_ADCAL) == ADC_CR_ADCAL) {};

	// Enable ADC
	ADC1->CR |= ADC_CR_ADEN;
	while ((ADC1->ISR & ADC_ISR_ADRDY) == 0) {}

	DMAMUX1_ChannelStatus->CFR |= DMAMUX_CFR_CSOF0; // Channel 1 Clear synchronization overrun event flag
	DMA1->IFCR = 0x3F << DMA_IFCR_CGIF1_Pos;		// clear all five interrupts for this stream

	DMA1_Channel1->CNDTR |= ADC_BUFFER_LENGTH;		// Number of data items to transfer (ie size of ADC buffer)
	DMA1_Channel1->CPAR = (uint32_t)(&(ADC1->DR));	// Configure the peripheral data register address 0x40022040
	DMA1_Channel1->CMAR = (uint32_t)(ADC_array);	// Configure the memory address (note that M1AR is used for double-buffer mode) 0x24000040

	DMA1_Channel1->CCR |= DMA_CCR_EN;				// Enable DMA and wait
	wait_loop_index = (SystemCoreClock / (100000UL * 2UL));
	while (wait_loop_index != 0UL) {
		wait_loop_index--;
	}

	ADC1->CR |= ADC_CR_ADSTART;						// Start ADC
}

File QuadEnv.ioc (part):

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Mcu.Name=STM32C031C(4-6)Tx
Mcu.Package=LQFP48
Mcu.UserName=STM32C031C6Tx
PA13.Mode=Serial_Wire
PA13.Signal=DEBUG_SWDIO
PA14-BOOT0.Mode=Serial_Wire
PA14-BOOT0.Signal=DEBUG_SWCLK
PA5.GPIOParameters=GPIO_Speed,PinState,GPIO_Label
PA5.GPIO_Label=Led
PA5.GPIO_Speed=GPIO_SPEED_FREQ_VERY_HIGH
PA5.PinState=GPIO_PIN_SET
PA5.Signal=GPIO_Output
PB6.Mode=Asynchronous
PB6.Signal=USART1_TX
PB7.Mode=Asynchronous
PB7.Signal=USART1_RX
PB8.Mode=I2C
PB8.Signal=I2C1_SCL
PB9.Mode=I2C
PB9.Signal=I2C1_SDA
PC13.GPIOParameters=GPIO_Label
PC13.GPIO_Label=User Button
PC13.Signal=GPXTI13
PC14-OSCX_IN\ (PC14).Mode=LSE-External-Oscillator
PC14-OSCX_IN\ (PC14).Signal=RCC_OSCX_IN
PC15-OSCX_OUT\ (PC15).Mode=LSE-External-Oscillator
PC15-OSCX_OUT\ (PC15).Signal=RCC_OSCX_OUT
PF0-OSC_IN\ (PF0).Mode=HSE-External-Oscillator
PF0-OSC_IN\ (PF0).Signal=RCC_OSC_IN
PF1-OSC_OUT\ (PF1).Mode=HSE-External-Oscillator
PF1-OSC_OUT\ (PF1).Signal=RCC_OSC_OUT
RCC.HSE_VALUE=48000000
RCC.SYSCLKFreq_VALUE=48000000
board=NUCLEO-C031C6
boardIOC=true

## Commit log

2023-03-04 Clock Initialisation
2023-03-04 ADC with DMA configured
2023-03-04 Cleaned up HAL and other unused libraries
2023-03-04 Created PWM Timer initialisation
2023-03-05 Created PWM interrupt; started converting envelope code
2023-03-05 Basic Envelope implementation Done
2023-03-05 Started roughing out component PCB layout
2023-03-06 Started adding UART
    Though tests show that UART1 is not connected by default on Nucleo
2023-03-06 UART2 tested working on Nucleo
2023-03-09 Completed first draft of components PCB
2023-03-10 First draft of control PCB complete
2023-03-10 First draft of Panel complete
2023-03-10 Tweaks to Panel
2023-03-11 Started creating firmware for STM32G431
2023-03-12 Added PWM Test code
2023-03-29 Clean up project for manufacture
    Fixed LED ordering bug on control board
2023-04-11 Corrections to schematic to fix sustain and release pots being switched
    +Updated project to use production module parts and connections
2023-04-11 Started tweaking envelope parameters from ADC
2023-04-13 Added configuration option to scale envelope times
    - Available from usb serial console
2023-04-13 Remove old project files relating to STM32C031
2023-04-14 Started adding readme;
    Clean CubeIDE project created to fix issues in current project
2023-04-14 Fixed spelling
2023-07-13 Cleaned up project structure
2023-08-18 Updated components and controls to include mode button/led
2023-08-20 Updated to version 2 of panel
2023-08-21 Completed v2 design
2023-08-21 Generated gerbers for v2 production
2023-08-21 Updated Gerbers and Ordered
2023-10-20 New component board with PWM LEDs; started refactor for invert button
2023-10-20 Implemented envelope inverting logic
2023-10-20 Clean up
2023-10-25 Started to merge with L4O code
2023-10-25 Long press on mode button will switch between envelope and lfo mode
2023-10-25 Separate fade in rates for LFO level and speed
2023-10-25 Update LFO verify config
2023-10-25 Moved L4O panel files into project; Updated Controls schematic to v2
2023-10-26 Renamed graphic
2023-10-26 Updated component schematic
2023-10-30 Updated firmware to output levels on PWM LEDs for v3 hardware
2023-10-31 Config manager outputs flash address info when saving
    Updated picture of QuadEnv panel
2023-10-31 Updated schematic
